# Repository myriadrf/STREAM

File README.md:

# STREAM

[STREAM](https://myriadrf.org/projects/stream/) is a flexible platform for developing high-performance digital and RF designs using an Altera Cyclone IV FPGA and Lime Microsystems FPRF transceiver.

The original STREAM board incorporates SDRAM, Micro SD storage and a selection of other useful peripherals, with expansion via RFDIO and FMC mezzanine cards enabling use with both LMS6002-based Myriad-RF 1 and UNITE LMS7002M EVB RF modules.

uSTREAM is a low cost variant that incorporates a uRFDIO connector, enabling use with the uMyriadRF-6002 and uMyriadRF-7002 RF modules.

For more details about compatible Myriad-RF transceiver modules, see the [Reference Development Kit](https://myriadrf.org/projects/rdk/).

## Contents

The directory structure is as follows:

      apps/
          lms6_usb_distro_03v/        - uSTREAM + uMyriadRF-6002 examples
          lms7_usb_distro_01v/        - uSTREAM + uMyriadRF-7002 examples
          STREAM_LMS7EVB_distro_07v/  - STREAM + UNITE LMS7002EVB examples

      docs/                      - platform documentation

      hardware/<variant>/<version>/
          BOM/                   - bill of materials spreadsheet
          Case/                  - Aluminium case design
          Gerbers/               - Gerber CAM files
          KiCAD/                 - KiCAD schematic and layout files
          Manufacturing/         - Additional manufacturing information
          PDF/                   - Schematic and layout PDFs
          Reports/               - DRC, ERC and drill reports
              
      stream_openrisc_soc/
          bin/                   - pre-built FPGA and Linux images
          doc/                   - HTML documentation for the Stream OpenRISC SoC
          quartus/               - Quartus project archive for rebuilding the FPGA image
          src/                   - Source code for Stream-specific cores
          sw/                    - Example applications for communicating with LMS6002D

## Licensing

### Hardware

The hardware designs are licensed under a Creative Commons Attribution 3.0 Unported licence.

### FPGA design

For details of the FPGA design licensing please see the associated COPYING file(s). However, please note that this does not extend to any files provided with the Altera design tools and see the relevant files for the associated terms and conditions.

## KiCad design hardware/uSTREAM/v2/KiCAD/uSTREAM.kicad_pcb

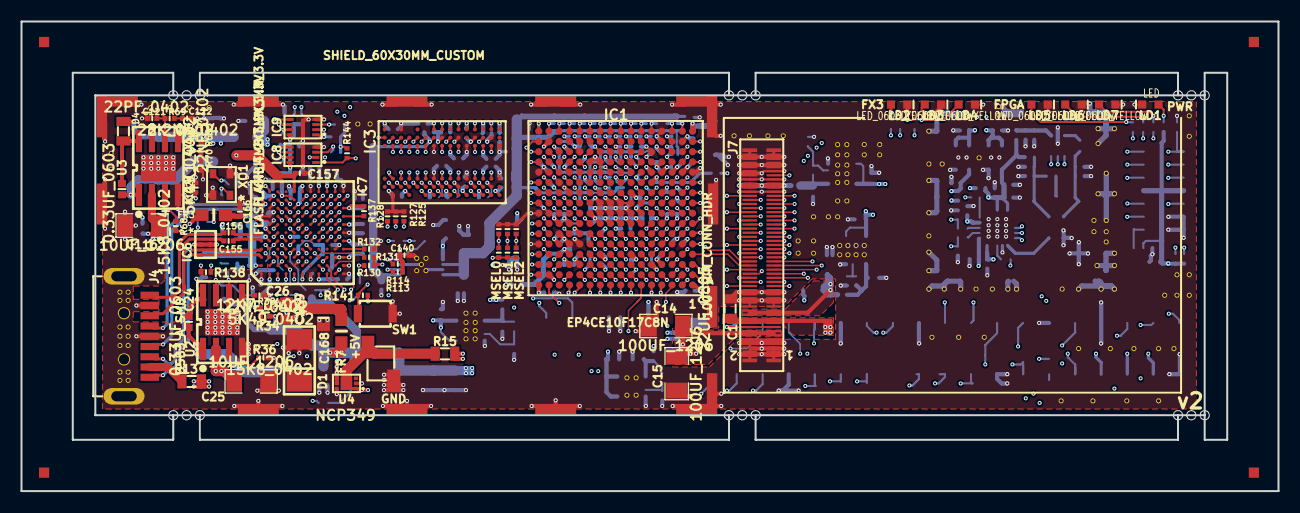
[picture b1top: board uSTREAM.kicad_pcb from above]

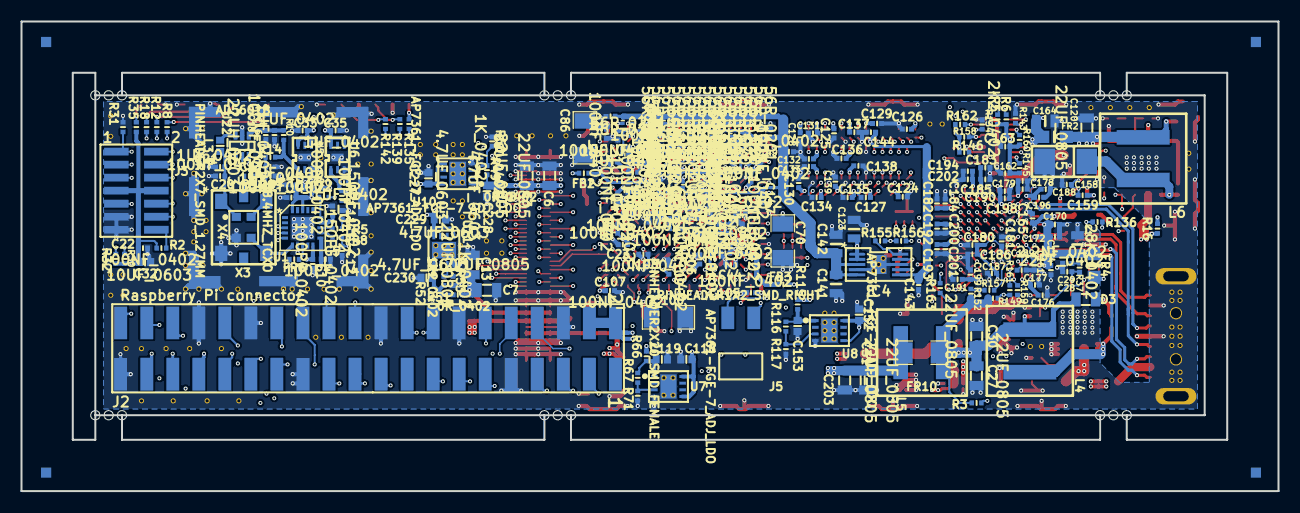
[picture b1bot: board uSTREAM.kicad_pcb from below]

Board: 12 copper layers, 122.6 x 45.8 mm, 491 parts (270 on the bottom side), 284 nets.

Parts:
BreakHole: VAL**; BreakHole
BreakHole#2, BreakHole#3, BreakHole#4, BreakHole#5, BreakHole#6, BreakHole#7, BreakHole#8, BreakHole#9, BreakHole#10, BreakHole#11, BreakHole#12, BreakHole#13, BreakHole#14, BreakHole#15, BreakHole#16, BreakHole#17, BreakHole#18: VAL**; BreakHole
C1, C3, C6, C7, C13, C27, C30, C31, C120, C203: 22UF_0805; SMD0805
C4, C5, C8, C9, C10: 100PF_0402; SMD0402
C11, C12: 150PF_0402; SMD0402
C14, C15: 100UF_1206; SMD1206
C16, C17, C20, C33, C34, C35, C36, C73, C76, C79, C82, C85, C96, C99: 1UF_0402; SMD0402
C18, C19, C21, C22, C23, C44, C64, C72, C75, C78, C81, C84, C87, C88, C89, C90, C91, C92, C95, C98, C101, C102, C103, C104, C105, C106, C107, C108, C109, C110, C112: 100NF_0402; SMD0402
C24, C115: 0.33UF_0603; SMD0603
C25, C116: 10UF_1206; SMD1206
C26, C117: 22NF_0402; SMD0402
C28, C121: 22PF_0402; SMD0402
C29, C122: 2.2NF_0402; SMD0402
C32: 10UF_0603; SMD0603
C70, C86, C100: 100UF_1206; SM1206
C71, C74, C77, C80, C83, C94, C97: 10NF_0402; SM0402
C113, C114, C124, C125, C126, C127, C128, C129, C130, C131, C132, C133, C134, C135, C136, C137, C138, C139, C143, C144, C146, C147, C148, C149, C150, C151, C155, C156, C161, C162, C163, C166, C170, C172, C174, C176, C178, C180, C182, C183, C186, C188, C189, C190, C191, C192, C193, C194: 100NF_0402; C_SM0402
C118, C119, C152, C153: 4.7UF_0603; C_SM0603
C123, C141, C142: 10UF_0805; C_SM0805
C140, C157: 1UF_0402; C_SM0402
C158, C159: 13PF_0402; C_SM0402
C164, C168, C169, C171: 22UF_0805; C_SM0805
C165, C177, C179, C181, C184, C185, C187, C196, C198, C199, C200, C201, C202: 10NF_0402; C_SM0402
C227, C228, C229, C230: 4.7UF_0603; SMD0603
D1, D2: 20BQ030; SMB
D3, D4: TS4148; SM0805
EK1: SHIELD_60X30MM_CUSTOM; shield_60x30mm_custom
EK2: SHIELD_16.5X16.5MM; shield_16.5x16.5mm
FB1, FB2, FB3, FB4: FB_600R_0402; R_SM0402
FD1, FD2, FD3, FD4: FIDUCIAL; Pad
FR2, FR3, FR4, FR7: FR_600R_0805_2A; R_SM0805
FR5, FR6, FR8, FR9: FR_220R_0402; R_SM0402
FR10: FR_220R_1206_4A; SM1206
GND_VIA: VAL**; GND_VIA
GND_VIA#2, GND_VIA#3, GND_VIA#4, GND_VIA#5, GND_VIA#6, GND_VIA#7, GND_VIA#8, GND_VIA#9, GND_VIA#10, GND_VIA#11, GND_VIA#12, GND_VIA#13, GND_VIA#14, GND_VIA#15, GND_VIA#16, GND_VIA#17, GND_VIA#18, GND_VIA#19, GND_VIA#20, GND_VIA#21, GND_VIA#22, GND_VIA#23, GND_VIA#24, GND_VIA#25, GND_VIA#26, GND_VIA#27, GND_VIA#28, GND_VIA#29, GND_VIA#30, GND_VIA#31, GND_VIA#32, GND_VIA#33, GND_VIA#34, GND_VIA#35, GND_VIA#36, GND_VIA#37, GND_VIA#38, GND_VIA#39, GND_VIA#40, GND_VIA#41, GND_VIA#42, GND_VIA#43, GND_VIA#44, GND_VIA#45, GND_VIA#46, GND_VIA#47, GND_VIA#48, GND_VIA#49, GND_VIA#50, GND_VIA#51, GND_VIA#52, GND_VIA#53, GND_VIA#54, GND_VIA#55, GND_VIA#56, GND_VIA#57, GND_VIA#58, GND_VIA#59, GND_VIA#60, GND_VIA#61, GND_VIA#62, GND_VIA#63, GND_VIA#64, GND_VIA#65, GND_VIA#66, GND_VIA#67, GND_VIA#68, GND_VIA#69, GND_VIA#70, GND_VIA#71, GND_VIA#72, GND_VIA#73, GND_VIA#74, GND_VIA#75, GND_VIA#76, GND_VIA#77, GND_VIA#78, GND_VIA#79, GND_VIA#80, GND_VIA#81, GND_VIA#82, GND_VIA#83, GND_VIA#84, GND_VIA#85, GND_VIA#86, GND_VIA#87, GND_VIA#88, GND_VIA#89, GND_VIA#90, GND_VIA#91, GND_VIA#92, GND_VIA#93, GND_VIA#94, GND_VIA#95, GND_VIA#96, GND_VIA#97, GND_VIA#98, GND_VIA#99, GND_VIA#100, GND_VIA#101, GND_VIA#102, GND_VIA#103, GND_VIA#104, GND_VIA#105, GND_VIA#106, GND_VIA#107, GND_VIA#108, GND_VIA#109, GND_VIA#110, GND_VIA#111, GND_VIA#112, GND_VIA#113, GND_VIA#114, GND_VIA#115, GND_VIA#116, GND_VIA#117, GND_VIA#118, GND_VIA#119, GND_VIA#120, GND_VIA#121, GND_VIA#122, GND_VIA#123, GND_VIA#124, GND_VIA#125, GND_VIA#126, GND_VIA#127: VAL**; GND_VIA
IC1: EP4CE10F17C8N; 256FBGA
IC3: W9751G6KB-25; 84WBGA
IC4: RT9026GFP; MSOP10
IC6: SP3010-04UTG; uDFN-10
IC7: CYUSB3013; FBGA_121_Ball_10x10
IC8, IC9: FLASH_4MBIT_2X3MM_3.3V; 8-USON
J1: JUMPER2_V; PINHEADER_1x2_SMD
J2: PINHEADER2X20_SMD_FEMALE; PinHeader2x20SMDfemale
J3: PINHEADER2X7_SMD_1.27MM; PinHeader2x7_SMD_1.27mm
J4: USB3_A_SMD
J5: PINHEADER1X2_SMD_RIGHT; PINHEADER_1x2_SMD_right
J7: 100-PIN_CONN_HDR
L3: 22UH_0603; SMD0603
L4: 2.2UH_XAL60XX_SERIES; XAL60xx series
L5: 22UH_XAL60XX_SERIES_NF; XAL60xx series
L6: 22UH_XAL60XX_SERIES; XAL60xx series
LD1: LED; LD0603
LD2, LD3, LD4, LD5, LD6, LD7: LED_0603_YELLOW; LD0603
R2, R141, R143: 100K_0402; R_SM0402
R3, R5, R6, R67: 2K2_0402; R_SM0402
R8, R12, R31, R71, R117, R135, R139, R142: 1K_0402; R_SM0402
R9, R18, R21, R66, R115, R132, R147, R150, R153, R156, R157, R159, R161, R163: 0R_0402; R_SM0402
R10, R14, R16: 100MHz/600/0.2A; R_SM0402
R13, R15: 0R_0805; SM0805
R20, R122, R148, R151, R154: 0R_0402_NF; R_SM0402
R22: 10K_0402; SMD0402
R30, R32, R113, R114, R125, R127, R128, R130, R149, R152, R155: 10K_0402; R_SM0402
R34: 12K7_0402; SMD0402
R35: 806R_0402; R_SM0402
R36, R68: 15K8_0402; SMD0402
R37, R69: 28K_0402; SMD0402
R38, R70: 5K49_0402; SMD0402
R48, R51: 0R_0402; SM0402
R49: 560_0402; SM0402
R50, R53: 1K_0402; SMD0402
R52: 1K2_0402; SM0402
R65: 1K1_0402; SMD0402
R72, R73, R74, R75, R76, R77, R78, R79, R80, R81, R82, R83, R84, R85, R86, R87, R88, R89, R90, R91, R92, R93, R94, R95, R96, R97, R98, R99, R100, R101, R102, R103, R104, R105, R106, R107, R108, R109, R110, R111, R112: 56R_0201; SMD0201
R116: 1K2_0402; R_SM0402
R131, R137: 10K_0402_NF; R_SM0402
R134: 2K2_0402; SMD0402
R136: 6.04K/1%_0402; R_SM0402
R138: 200R/1%_0402; R_SM0402
R144, R145, R146, R158, R160, R162: 4K7_0402; R_SM0402
SW1: SW_TACTILE; SW_B3U-1000P
U1: SI5351C; QFN20
U2, U3: SC4524; SOIC-8
U4: NCP349; 6-DFN
U5: LP5900SD-3.3; SC70
U6: LP5900SD-1.8; SC70
U7, U8, U10, U11: AP7361-FGE-7_ADJ_LDO; 8-UDFN3030
U22: AD5601B; SC-70-6
X3: RACON_TXCO_PLUTO+; SMD_TXCO_Pluto+
X4: 38.4MHZ_TCXO; TCXO_2x2.5mm
XO1: CRYSTAL_19.2MHZ; 4-SMD_TCXO

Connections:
+1.8V: C7.1, C13.1, J7.21, J7.22, J7.23, J7.24, R51.2
+1.8VD: C86.1, C87.1, C88.1, C89.1, C90.1, C91.1, C92.1, C101.1, C102.1, C103.1, C104.1, C123.1, C124.1, C125.1, C126.1, C127.1, C128.1, C129.1, C130.1, C131.1, C132.1, C133.1, C134.1, C135.1, C136.1, C137.1, C138.1, C139.1, C182.1, C183.1, C184.1, C185.1, IC1.E14, IC1.G14, IC1.K14, IC1.M14, IC1.P4, IC1.P7, IC1.P10, IC1.P13, IC1.T1, IC1.T16, IC3.A1, IC3.A9, IC3.C1, IC3.C3, IC3.C7, IC3.C9, IC3.E1, IC3.E9, IC3.G1, IC3.G3, IC3.G7, IC3.G9, IC3.J1, IC3.J9, IC3.M9, IC3.R1, IC4.1, IC4.2, IC7.H11, IC7.L9, R115.2, R130.2, R131.2, R137.2
+1.8V_CLK: C10.1, C36.1, R21.2, U1.10, U6.1
+1.25V: C3.1, C6.1, J7.83, J7.84, J7.85, J7.86, R48.2
+3.3VD: C23.1, C27.1, C30.1, C44.1, C64.1, C100.1, C105.1, C106.1, C107.1, C108.1, C109.1, C110.1, C112.1, C140.1, C152.1, C162.1, C163.1, D3.1, FR3.2, FR7.1, FR10.1, IC1.A1, IC1.A16, IC1.C4, IC1.C7, IC1.C10, IC1.C13, IC1.E3, IC1.G3, IC1.K3, IC1.M3, IC4.10, IC8.8, IC9.8, L4.1, L5.2, R3.1, R5.1, R6.1, R22.1, R34.1, R113.1, R114.1, R141.2, R144.1, R145.1, R146.1, R149.1, R152.1, R155.1, R158.1, R160.1, R162.1, U8.5, U8.8
+3.3V_CLK: C4.1, C8.1, C9.1, C34.1, R10.2, R14.2, R20.2, U1.14, U1.18, U1.20, U5.1
+3.3Va: C1.1, C22.1, C31.1, C32.1, C118.1, C203.1, C227.1, C229.1, FR10.2, J3.7, J3.8, J7.17, J7.18, J7.19, J7.20, L5.1, R2.2, R30.2, R32.2, R35.2, U7.5, U7.8, U10.5, U10.8, U11.5, U11.8
+5V: C14.1, C15.1, C25.1, C33.1, C35.1, C116.1, J7.11, J7.12, J7.13, J7.14, R16.1, U2.2, U3.2, U4.4, U4.5, U5.4, U5.6, U6.4, U6.6
+5V_RPi: J2.2, J2.4, R15.2
+5V_USB: J4.1, R13.1
/FX3/D+: IC7.A9, J4.3
/FX3/D-: IC7.A10, J4.2
/FX3/FX3_FLASH1_SNN: IC7.C1, J5.2
/FX3/FX3_FLASH2_SNN: IC7.F2, IC9.1, R158.2
/FX3/FX3_LED0: IC7.H2, R135.1
/FX3/FX3_LED1: IC7.H3, R139.1
/FX3/FX3_LED2: IC7.K1, R142.1
/FX3/MSEL0: IC1.H13, R147.1, R148.2
/FX3/MSEL1: IC1.H12, R150.1, R151.2
/FX3/MSEL2: IC1.G12, R153.1, R154.2
/FX3/OTG_ID: IC7.C9, R122.1
/FX3/SSRX+: IC6.5, IC6.6, IC7.A3, J4.9
/FX3/SSRX-: IC6.4, IC6.7, IC7.A4, J4.8
/FX3/SSTX+: C155.1, IC6.2, IC6.9, J4.6
/FX3/SSTX-: C156.1, IC6.1, IC6.10, J4.5
/LMS Digital Circuits/CLK_IO: C5.1, R20.1, R21.1, U1.11
/RaspberryPi_Connector/LD5: IC1.E11, R8.1
/RaspberryPi_Connector/LD6: IC1.E10, R12.1
/RaspberryPi_Connector/RPI_CE0n: IC1.A7, J2.24
/RaspberryPi_Connector/RPI_CE1n: IC1.C9, J2.26
/RaspberryPi_Connector/RPI_GCLK: IC1.B13, J2.7
/RaspberryPi_Connector/RPI_GEN0: IC1.D12, J2.11
/RaspberryPi_Connector/RPI_GEN1: IC1.A12, J2.12
/RaspberryPi_Connector/RPI_GEN2: IC1.B12, J2.13
/RaspberryPi_Connector/RPI_GEN3: IC1.A11, J2.15
/RaspberryPi_Connector/RPI_GEN4: IC1.B11, J2.16
/RaspberryPi_Connector/RPI_GEN5: IC1.A10, J2.18
/RaspberryPi_Connector/RPI_GEN6: IC1.B9, J2.22
/RaspberryPi_Connector/RPI_GPIO5: IC1.B8, J2.29
/RaspberryPi_Connector/RPI_GPIO6: IC1.D9, J2.31
/RaspberryPi_Connector/RPI_GPIO12: IC1.D8, J2.32
/RaspberryPi_Connector/RPI_GPIO13: IC1.F11, J2.33
/RaspberryPi_Connector/RPI_GPIO16: IC1.E8, J2.36
/RaspberryPi_Connector/RPI_GPIO19: IC1.E9, J2.35
/RaspberryPi_Connector/RPI_GPIO20: IC1.F8, J2.38
/RaspberryPi_Connector/RPI_GPIO21: IC1.F9, J2.40
/RaspberryPi_Connector/RPI_GPIO26: IC1.F10, J2.37
/RaspberryPi_Connector/RPI_ID_SC: IC1.C8, J2.28
/RaspberryPi_Connector/RPI_ID_SD: IC1.D11, J2.27
/RaspberryPi_Connector/RPI_MISO: IC1.A9, J2.21
/RaspberryPi_Connector/RPI_MOSI: IC1.B10, J2.19
/RaspberryPi_Connector/RPI_RXD0: IC1.C11, J2.10
/RaspberryPi_Connector/RPI_SCLK: IC1.A8, J2.23
/RaspberryPi_Connector/RPI_TXD0: IC1.C6, J2.8
/RaspberryPi_Connector/VCCA1: C97.1, C98.1, C99.1, FB2.2, IC1.L5
/RaspberryPi_Connector/VCCA2: C94.1, C95.1, C96.1, FB1.2, IC1.F12
/RaspberryPi_Connector/VCCD_PLL1: C83.1, C84.1, C85.1, FB4.2, IC1.N4
/RaspberryPi_Connector/VCCD_PLL2: C80.1, C81.1, C82.1, FB3.2, IC1.D13
DDR_A0: IC1.K10, IC3.M8, R92.2
DDR_A1: IC1.T8, IC3.M3, R93.2
DDR_A2: IC1.L9, IC3.M7, R94.2
DDR_A3: IC1.T10, IC3.N2, R95.2
DDR_A4: IC1.N3, IC3.N8, R96.2
DDR_A5: IC1.T9, IC3.N3, R97.2
DDR_A6: IC1.K9, IC3.N7, R98.2
DDR_A7: IC1.T15, IC3.P2, R99.2
DDR_A8: IC1.P14, IC3.P8, R100.2
DDR_A9: IC1.T11, IC3.P3, R101.2
DDR_A10: IC1.T6, IC3.M2, R102.2
DDR_A11: IC1.R13, IC3.P7, R103.2
DDR_A12: IC1.T14, IC3.R2, R104.2
DDR_B0: IC1.T5, IC3.L2, R105.2
DDR_B1: IC1.T3, IC3.L3, R106.2
DDR_CKE: IC1.T2, IC3.K2, R112.2
DDR_CLKn: IC1.N12, IC3.K8
DDR_CLKp: IC1.M11, IC3.J8
DDR_DQ0: IC1.N6, IC3.G8, R72.2
DDR_DQ1: IC1.R6, IC3.G2, R73.2
DDR_DQ2: IC1.N5, IC3.H7, R74.2
DDR_DQ3: IC1.R7, IC3.H3, R75.2
DDR_DQ4: IC1.R5, IC3.H1, R76.2
DDR_DQ5: IC1.L7, IC3.H9, R77.2
DDR_DQ6: IC1.R3, IC3.F1, R78.2
DDR_DQ7: IC1.L8, IC3.F9, R79.2
DDR_DQ8: IC1.R11, IC3.C8, R80.2
DDR_DQ9: IC1.R10, IC3.C2, R81.2
DDR_DQ10: IC1.N8, IC3.D7, R82.2
DDR_DQ11: IC1.R12, IC3.D3, R83.2
DDR_DQ12: IC1.T12, IC3.D1, R84.2
DDR_DQ13: IC1.N9, IC3.D9, R85.2
DDR_DQ14: IC1.T13, IC3.B1, R86.2
DDR_DQ15: IC1.P8, IC3.B9, R87.2
DDR_LDM: IC1.P3, IC3.F3, R90.2
DDR_LDQS: IC1.M7, IC3.F7, R88.2
DDR_ODT: IC1.R8, IC3.K9, R111.2
DDR_UDM: IC1.M8, IC3.B3, R91.2
DDR_UDQS: IC1.T7, IC3.B7, R89.2
DDR_nCAS: IC1.L11, IC3.L7, R108.2
DDR_nCS: IC1.L10, IC3.L8, R110.2
DDR_nRAS: IC1.M9, IC3.K7, R107.2
DDR_nWE: IC1.R9, IC3.K3, R109.2
DIG_RST: IC1.D6, J7.44
DIQ1_D0: IC1.L1, J7.74
DIQ1_D1: IC1.L2, J7.76
DIQ1_D2: IC1.P1, J7.79
DIQ1_D3: IC1.K1, J7.72
DIQ1_D4: IC1.K5, J7.70
DIQ1_D5: IC1.L6, J7.78
DIQ1_D6: IC1.P2, J7.77
DIQ1_D7: IC1.R1, J7.75
DIQ1_D8: IC1.K6, J7.68
DIQ1_D9: IC1.N2, J7.73
DIQ1_D10: IC1.L4, J7.80
DIQ1_D11: IC1.J1, J7.66
DIQ2_D0: IC1.D4, J7.52
DIQ2_D1: IC1.B6, J7.49
DIQ2_D2: IC1.D3, J7.50
DIQ2_D3: IC1.B1, J7.51
DIQ2_D4: IC1.F2, J7.56
DIQ2_D5: IC1.E5, J7.54
DIQ2_D6: IC1.F1, J7.58
DIQ2_D7: IC1.B3, J7.53
DIQ2_D8: IC1.G1, J7.60
DIQ2_D9: IC1.C1, J7.55
DIQ2_D10: IC1.J2, J7.64
DIQ2_D11: IC1.G2, J7.62
ENABLE_IQSEL1: IC1.J6, J7.67
ENABLE_IQSEL2: IC1.C3, J7.59
FCLK1: IC1.K2, J7.69
FCLK2: IC1.D2, J7.61
FPGA_CLK4: FR6.2, IC1.E15
FPGA_CONF_DONE: IC1.H14, R155.2, R156.1
FPGA_DAC_CS: IC1.B5, U22.1
FPGA_DATA0: IC1.H2, R159.1
FPGA_DCLK: IC1.H1, R163.1
FPGA_LMS_CS: IC1.A2, J7.38
FPGA_NCONFIG: IC1.H5, R149.2, R161.1
FPGA_NSTATUS: IC1.F4, R152.2, R157.1
FPGA_SPI_MISO: IC1.E6, J7.37
FPGA_SPI_MOSI: IC1.A5, J7.36, U22.3
FPGA_SPI_SCK: IC1.E7, J7.40, U22.2
FX3_CONF_DONE: IC7.E5, R156.2
FX3_CTL0: IC1.K15, IC7.K8
FX3_CTL1: IC1.J15, IC7.K7
FX3_CTL2: IC1.F13, IC7.J7
FX3_CTL3: IC1.D15, IC7.H7
FX3_CTL4: IC1.B16, IC7.G7
FX3_CTL5: IC1.F15, IC7.G6
FX3_CTL6: IC1.J14, IC7.K6
FX3_CTL7: IC1.J12, IC7.H8
FX3_CTL8: IC1.G16, IC7.G5
FX3_CTL9: IC1.C16, IC7.H6
FX3_CTL10: IC1.J16, IC7.K5
FX3_CTL11: IC1.J13, IC7.J5
FX3_CTL12: IC1.G15, IC7.H5
FX3_DATA0: IC7.D1, R159.2
FX3_DCLK: IC7.D3, R163.2
FX3_DQ0: IC1.P16, IC7.F10
FX3_DQ1: IC1.R16, IC7.F9
FX3_DQ2: IC1.F16, IC7.F7
FX3_DQ3: IC1.N13, IC7.G10
FX3_DQ4: IC1.K11, IC7.G9
FX3_DQ5: IC1.J11, IC7.F8
FX3_DQ6: IC1.N15, IC7.H10
FX3_DQ7: IC1.K12, IC7.H9
FX3_DQ8: IC1.N16, IC7.J10
FX3_DQ9: IC1.L16, IC7.J9
FX3_DQ10: IC1.M12, IC7.K11
FX3_DQ11: IC1.L15, IC7.L10
FX3_DQ12: IC1.L13, IC7.K10
FX3_DQ13: IC1.L12, IC7.K9
FX3_DQ14: IC1.K16, IC7.J8
FX3_DQ15: IC1.G11, IC7.G8
FX3_FPGA_GPIO0: IC1.B4, IC7.K2
FX3_FPGA_GPIO1: IC1.A4, IC7.J2
FX3_FPGA_GPIO2: IC1.D5, IC7.J3
FX3_FPGA_GPIO3: IC1.A3, IC7.J1
FX3_FPGA_SNN: IC1.A6, IC7.E1
FX3_NCONFIG: IC7.D2, R161.2
FX3_NSTATUS: IC7.E4, R157.2
FX3_PCLK: IC1.D16, IC7.J6
FX3_SPI_MISO: IC1.F6, IC7.C2, IC8.2, IC9.2, R134.1
FX3_SPI_MOSI: IC1.F7, IC7.D5, IC8.5, IC9.5
FX3_SPI_SCK: IC1.B7, IC7.D4, IC8.6, IC9.6, R143.1
FX3_VCC3P3: C168.1, C169.1, C176.1, C177.1, C178.1, C179.1, C180.1, C181.1, C186.1, C187.1, FR7.2, IC7.B1, IC7.C11, IC7.E3, IC7.E10, IC7.F1
FX3_VDD: C164.1, C188.1, C189.1, C190.1, C191.1, C192.1, C193.1, C194.1, C196.1, C198.1, C199.1, C200.1, C201.1, C202.1, FR2.2, FR4.2, IC7.B10, IC7.C3, IC7.E9, IC7.F11, IC7.H1, IC7.J11, IC7.L5, IC7.L7
GND: C1.2, C3.2, C4.2, C5.2, C6.2, C7.2, C8.2, C9.2, C10.2, C11.2, C12.2, C13.2, C14.2, C15.2, C16.2, C17.2, C18.2, C19.2, C20.2, C21.2, C22.2, C23.2, C25.2, C26.2, C27.2, C28.2, C29.2, C30.2, C31.2, C32.2, C33.2, C34.2, C35.2, C36.2, C44.2, C64.2, C70.2, C71.2, C72.2, C73.2, C74.2, C75.2, C76.2, C77.2, C78.2, C79.2, C80.2, C81.2, C82.2, C83.2, C84.2, C85.2, C86.2, C87.2, C88.2, C89.2, C90.2, C91.2, C92.2, C94.2, C95.2, C96.2, C97.2, C98.2, C99.2, C100.2, C101.2, C102.2, C103.2, C104.2, C105.2, C106.2, C107.2, C108.2, C109.2, C110.2, C112.2, C113.2, C114.2, C116.2, C117.2, C118.2, C119.2, C120.2, C121.2, C122.2, C123.2, C124.2, C125.2, C126.2, C127.2, C128.2, C129.2, C130.2, C131.2, C132.2, C133.2, C134.2, C135.2, C136.2, C137.2, C138.2, C139.2, C140.2, C141.2, C142.2, C143.2, C144.2, C146.2, C147.2, C148.2, C149.2, C150.2, C151.2, C152.2, C153.2, C157.2, C158.1, C159.1, C161.2, C162.2, C163.2, C164.2, C165.2, C166.2, C168.2, C169.2, C170.2, C171.2, C172.2, C174.2, C176.2, C177.2, C178.2, C179.2, C180.2, C181.2, C182.2, C183.2, C184.2, C185.2, C186.2, C187.2, C188.2, C189.2, C190.2, C191.2, C192.2, C193.2, C194.2, C196.2, C198.2, C199.2, C200.2, C201.2, C202.2, C203.2, C227.2, C228.2, C229.2, C230.2, D1.1, D2.1, EK1.1, EK2.1, GND_VIA.1, GND_VIA#2.1, GND_VIA#3.1, GND_VIA#4.1, GND_VIA#5.1, GND_VIA#6.1, GND_VIA#7.1, GND_VIA#8.1, GND_VIA#9.1, GND_VIA#10.1, GND_VIA#11.1, GND_VIA#12.1, GND_VIA#13.1, GND_VIA#14.1, GND_VIA#15.1, GND_VIA#16.1, GND_VIA#17.1, GND_VIA#18.1, GND_VIA#19.1, GND_VIA#20.1, GND_VIA#21.1, GND_VIA#22.1, GND_VIA#23.1, GND_VIA#24.1, GND_VIA#25.1, GND_VIA#26.1, GND_VIA#27.1, GND_VIA#28.1, GND_VIA#29.1, GND_VIA#30.1, GND_VIA#31.1, GND_VIA#32.1, GND_VIA#33.1, GND_VIA#34.1, GND_VIA#35.1, GND_VIA#36.1, GND_VIA#37.1, GND_VIA#38.1, GND_VIA#39.1, GND_VIA#40.1, GND_VIA#41.1, GND_VIA#42.1, GND_VIA#43.1, GND_VIA#44.1, GND_VIA#45.1, GND_VIA#46.1, GND_VIA#47.1, GND_VIA#48.1, GND_VIA#49.1, GND_VIA#50.1, GND_VIA#51.1, GND_VIA#52.1, GND_VIA#53.1, GND_VIA#54.1, GND_VIA#55.1, GND_VIA#56.1, GND_VIA#57.1, GND_VIA#58.1, GND_VIA#59.1, GND_VIA#60.1, GND_VIA#61.1, GND_VIA#62.1, GND_VIA#63.1, GND_VIA#64.1, GND_VIA#65.1, GND_VIA#66.1, GND_VIA#67.1, GND_VIA#68.1, GND_VIA#69.1, GND_VIA#70.1, GND_VIA#71.1, GND_VIA#72.1, GND_VIA#73.1, GND_VIA#74.1, GND_VIA#75.1, GND_VIA#76.1, GND_VIA#77.1, GND_VIA#78.1, GND_VIA#79.1, GND_VIA#80.1, GND_VIA#81.1, GND_VIA#82.1, GND_VIA#83.1, GND_VIA#84.1, GND_VIA#85.1, GND_VIA#86.1, GND_VIA#87.1, GND_VIA#88.1, GND_VIA#89.1, GND_VIA#90.1, GND_VIA#91.1, GND_VIA#92.1, GND_VIA#93.1, GND_VIA#94.1, GND_VIA#95.1, GND_VIA#96.1, GND_VIA#97.1, GND_VIA#98.1, GND_VIA#99.1, GND_VIA#100.1, GND_VIA#101.1, GND_VIA#102.1, GND_VIA#103.1, GND_VIA#104.1, GND_VIA#105.1, GND_VIA#106.1, GND_VIA#107.1, GND_VIA#108.1, GND_VIA#109.1, GND_VIA#110.1, GND_VIA#111.1, GND_VIA#112.1, GND_VIA#113.1, GND_VIA#114.1, GND_VIA#115.1, GND_VIA#116.1, GND_VIA#117.1, GND_VIA#118.1, GND_VIA#119.1, GND_VIA#120.1, GND_VIA#121.1, GND_VIA#122.1, GND_VIA#123.1, GND_VIA#124.1, GND_VIA#125.1, GND_VIA#126.1, GND_VIA#127.1, IC1.B2, IC1.B15, IC1.C5, IC1.C12, IC1.D7, IC1.D10, IC1.E2, IC1.E4, IC1.E12, IC1.E13, IC1.E16, IC1.F14, IC1.G4, IC1.G13, IC1.H7, IC1.H8, IC1.H9, IC1.H10, IC1.H15, IC1.H16, IC1.J3, IC1.J7, IC1.J8, IC1.J9, IC1.J10, IC1.K4, IC1.K13, IC1.L14, IC1.M1, IC1.M2, IC1.M4, IC1.M5, IC1.M10, IC1.M13, IC1.M15, IC1.M16, IC1.N7, IC1.N10, IC1.N11, IC1.P5, IC1.P12, IC1.R2, IC1.R4, IC1.R15, IC1.T4, IC3.A3, IC3.A7, IC3.B2, IC3.B8, IC3.D2, IC3.D8, IC3.E3, IC3.E7, IC3.F2, IC3.F8, IC3.H2, IC3.H8, IC3.J3, IC3.J7, IC3.N1, IC3.P9, IC4.4, IC4.8, IC4.11, IC6.3, IC6.8, IC7.A1, IC7.A8, IC7.B7, IC7.B8, IC7.B9, IC7.D8, IC7.E2, IC7.G1, IC7.G11, IC7.K3, IC7.K4, IC7.L1, IC7.L2, IC7.L3, IC7.L6, IC7.L11, IC8.4, IC8.9, IC9.4, IC9.9, J1.1, J2.6, J2.9, J2.14, J2.20, J2.25, J2.30, J2.34, J2.39, J3.11, J3.13, J4.4, J4.7, J4.10, J7.0, J7.1, J7.2, J7.3, J7.4, J7.5, J7.6, J7.7, J7.8, J7.9, J7.10, J7.15, J7.16, J7.25, J7.26, J7.27, J7.28, J7.29, J7.30, J7.31, J7.32, J7.33, J7.34, J7.81, J7.82, J7.87, J7.88, J7.90, J7.91, J7.92, J7.93, J7.94, J7.95, J7.96, J7.97, J7.98, J7.99, J7.100, LD1.2, LD2.2, LD3.2, LD4.2, LD5.2, LD6.2, LD7.2, R31.1, R36.2, R38.2, R50.1, R53.1, R68.2, R70.2, R71.2, R117.2, R122.2, R125.1, R127.1, R128.1, R132.2, R134.2, R136.2, R138.2, R143.2, R147.2, R150.2, R153.2, SW1.1, U1.7, U1.21, U2.4, U2.9, U3.4, U3.9, U4.2, U4.6, U5.3, U5.7, U6.3, U6.7, U7.4, U7.9, U8.4, U8.9, U10.4, U10.9, U11.4, U11.9, U22.5, X3.2, X4.2, XO1.2, XO1.4
GPIO0: IC1.P9, J7.39
GPIO1: IC1.L3, J7.41
GPIO2: IC1.N14, J7.43
GPIO3: IC1.P15, J7.45
G_PWR_DWN: IC1.D1, J7.46
I2C_SCL: IC1.C14, IC7.D9, J2.5, R6.2, U1.4
I2C_SDA: IC1.D14, IC7.D10, J2.3, R5.2, U1.5
LD7: IC1.K8, R18.1
MCLK1: IC1.N1, J7.71
MCLK2: IC1.C2, J7.57
unnamed: J3.14, R2.1
unnamed: U1.6, X3.4, X4.3
unnamed: FR6.1, U1.8
unnamed: FR9.1, U1.15
unnamed: FR8.1, U1.12
unnamed: FR9.2, IC1.E1
unnamed: FR5.1, U1.13
unnamed: C16.1, C18.1, R10.1, U22.4
unnamed: R9.1, X3.6
unnamed: L3.2, U22.6
unnamed: C17.1, C19.1, R9.2, R14.1, X3.5, X4.4
unnamed: C20.1, C21.1, L3.1, X3.1, X4.1
unnamed: C158.2, IC7.C7, XO1.3
unnamed: C159.2, IC7.C6, XO1.1
unnamed: IC7.B3, R138.1
unnamed: IC7.E6, R128.2
unnamed: IC7.B4, R127.2
unnamed: C161.1, IC7.C5, R141.1, SW1.2
unnamed: C156.2, IC7.A6
unnamed: IC7.L4, R132.1
unnamed: IC7.G4, R130.1
unnamed: IC7.H4, R131.1
unnamed: LD3.1, R139.2
unnamed: IC7.L8, R137.1
unnamed: IC9.7, R160.2
unnamed: IC9.3, R162.2
unnamed: IC7.C8, R136.1
unnamed: LD2.1, R135.2
unnamed: LD4.1, R142.2
unnamed: IC8.3, R146.2
unnamed: IC8.7, R145.2
unnamed: IC8.1, J5.1, R144.2
unnamed: C155.2, IC7.A5
unnamed: C157.1, IC7.E11, R16.2
unnamed: IC7.B2, R125.2
unnamed: C170.1, C171.1, C172.1, C174.1, FR4.1, IC7.A2, IC7.A7, IC7.B5
unnamed: C165.1, C166.1, FR3.1, IC7.B6
unnamed: LD7.1, R18.2
unnamed: LD6.1, R12.2
unnamed: LD5.1, R8.2
unnamed: IC4.9, R114.2
unnamed: IC4.7, R113.2
unnamed: C117.1, U3.5
unnamed: R68.1, U3.3
unnamed: C122.1, R69.2
unnamed: C115.2, D2.2, L6.2, U3.1
unnamed: C115.1, D4.2, U3.8
unnamed: C121.1, R69.1, U3.6
unnamed: R65.2, R70.1, U3.7
unnamed: C119.1, R66.1, R67.1, U7.1
unnamed: R67.2, R71.1, U7.3
unnamed: C153.1, R115.1, R116.2, U8.1
unnamed: C228.1, R48.1, R49.1, U10.1
unnamed: C230.1, R51.1, R52.2, U11.1
unnamed: R116.1, R117.1, U8.3
unnamed: C24.1, D3.2, U2.8
unnamed: C28.1, R37.1, U2.6
unnamed: R36.1, U2.3
unnamed: C26.1, U2.5
unnamed: R34.2, R38.1, U2.7
unnamed: C24.2, D1.2, L4.2, U2.1
unnamed: C29.1, R37.2
unnamed: R52.1, R53.2, U11.3
unnamed: R49.2, R50.2, U10.3
unnamed: J1.2, R13.2, R15.1, U4.1
unnamed: LD1.1, R35.1
RESET: IC1.F3, J7.42, R22.2
RXPLL_CLK: C11.1, FR5.2, J7.89
RX_EN: IC1.A15, J7.47
Synt_INTR: IC7.F4, R3.2, U1.3
TCK_FPGA: IC1.H3, J3.5, R32.1
TCK_FX3: IC7.F6, J3.2
TDI_FPGA: IC1.H4, J3.9, R30.1
TDI_FX3: IC7.E7, J3.6
TDO_FPGA: IC1.J4, J3.1, R31.2
TDO_FX3: IC7.C10, J3.10
TMS_FPGA: IC1.J5, J3.3
TMS_FX3: IC7.E8, J3.4
TRST_N_FX3: IC7.B11, J3.12
TXNRX1: IC1.F5, J7.65
TXNRX2: IC1.G5, J7.63
TXPLL_CLK: C12.1, FR8.2, J7.35
TX_EN: IC1.A13, J7.48
VCC1P2: C70.1, C71.1, C72.1, C73.1, C74.1, C75.1, C76.1, C77.1, C78.1, C79.1, C120.1, D4.1, FB3.1, FB4.1, FR2.1, IC1.G6, IC1.G7, IC1.G8, IC1.G9, IC1.G10, IC1.H6, IC1.H11, IC1.K7, L6.1, R65.1
VCC2P5: FB1.1, FB2.1, R66.2, R148.1, R151.1, R154.1
VREF_B3_B4: C113.1, C114.1, C143.1, C144.1, IC1.P6, IC1.P11, IC3.J2, IC4.6
VTT_SDRAM: C141.1, C142.1, C146.1, C147.1, C148.1, C149.1, C150.1, C151.1, IC4.3, IC4.5, R72.1, R73.1, R74.1, R75.1, R76.1, R77.1, R78.1, R79.1, R80.1, R81.1, R82.1, R83.1, R84.1, R85.1, R86.1, R87.1, R88.1, R89.1, R90.1, R91.1, R92.1, R93.1, R94.1, R95.1, R96.1, R97.1, R98.1, R99.1, R100.1, R101.1, R102.1, R103.1, R104.1, R105.1, R106.1, R107.1, R108.1, R109.1, R110.1, R111.1, R112.1

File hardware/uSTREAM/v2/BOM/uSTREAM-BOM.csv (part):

0.33UF_0603	2	"C24 C115"	SMD0603	Farnell	1759404RL	MULTICOMP	MCCA000526	MLCC 0603 X5R 16V 0.33UF	0.33uF
2.2NF_0402	2	"C29 C122"	SMD0402	Digi-Key	1276-1054-1-ND	Samsung Electro-Mechanics America, Inc	CL05B222KB5NNNC	CAP CER 2200PF 50V 10% X7R 0402	2.2nF
4.7UF_0603	8	"C118 C119 C152 C153 C227 C228 C229 C230"	SMD0603	Digi-Key	1276-2087-1-ND	Samsung Electro-Mechanics America, Inc.	CL10B475KQ8NQNC	CAP CER 4.7UF 6.3V X7R 0603	4.7uF
100NF_0402	31	"C113 C114 C124 C125 C126 C127 C128 C129 C130 C131 C132 C133 C134 C135 C136 C137 C138 C139 C143 C144 C146 C147 C148 C149 C150 C151 C155 C156 C161 C162 C163"	C_SM0402	DigiKey	399-3027-1-ND	KEMET	C0402C104K8PACTU	CAP, CER, 0.1UF, 10V, 10%, X5R, 0402,	100nF
1UF_0402	1	"C140"	C_SM0402	Digi-Key	311-1377-1-ND	Yageo	CC0402ZRY5V5BB105	CAP, CER, 1UF, 6.3V, Y5V, 0402,	1uF
1UF_0402	1	"C157"	C_SM0402	Digi-Key	490-6298-1-ND	Murata Electronics North America	GRM155R61A105KE15J	CAP, CER, 1UF, 10V, 10%, X5R, 0402,	1uF
13PF_0402	2	"C158 C159"	C_SM0402	DigiKey	490-5925-1-ND	Murata Electronics North America	GRM1555C1H130JA01D	CAP CER, 13PF, 50V, 5%, NPO, 0402,	13pF
10NF_0402	13	"C165 C177 C179 C181 C184 C185 C187 C196 C198 C199 C200 C201 C202"	C_SM0402	DigiKey	311-1349-1-ND	Yageo	CC0402KRX7R9BB103	CAP CER, 10000PF, 50V, 10%, X7R, 0402,	10nF
100NF_0402	17	"C166 C170 C172 C174 C176 C178 C180 C182 C183 C186 C188 C189 C190 C191 C192 C193 C194"	C_SM0402	DigiKey	399-3027-1-ND	KEMET	C0402C104K8PACTU	CAP, CER, 0.1UF, 10V, 10%, X5R, 0402,	100nF
10UF_0805	3	"C123 C141 C142"	C_SM0805	Digi-Key	445-11388-1-ND	TDK Corporation	C2012JB0J106K125AB	CAP CER, 10UF, 6.3V, 10%, JB, 0805,	10uF
22UF_0805	4	"C164 C168 C169 C171"	C_SM0805	Digi-Key	587-1958-1-ND	Taiyo Yuden	LMK212BJ226MG-T	CAP CER, 22UF, 10V, 20%, X5R, 0805,	22uF
100UF_1206	4	"C14 C70 C86 C100"	C_SM1206	DigiKey	490-4539-1-ND	Murata Electronics North America	GRM31CR60J107ME39L	CAP CER, 100UF, 6.3V, 20%, X5R, 1206,	100uF
100UF_1206_NF	1	"C15"	C_SM1206	DigiKey	490-4539-1-ND	Murata Electronics North America	GRM31CR60J107ME39L	CAP CER, 100UF, 6.3V, 20%, X5R, 1206,	100uF NF	NOFIT
10NF_0402	7	"C71 C74 C77 C80 C83 C94 C97"	SM0402	DigiKey	311-1349-1-ND	Yageo	CC0402KRX7R9BB103	CAP CER, 10000PF, 50V, 10%, X7R, 0402,	10nF
100PF_0402	5	"C4 C5 C8 C9 C10"	SMD0402	Digi-Key	311-1024-1-ND	Yageo	CC0402JRNPO9BN101	CAP CER, 100PF, 50V, 5%, NPO, 0402,	100pF
150PF_0402	2	"C11 C12"	SMD0402	Digi-Key	587-1213-1-ND	Taiyo Yuden	UMK105CG151JV-F	CAP CER 150PF 50V NP0 0402	150pF
1UF_0402	14	"C16 C17 C20 C33 C34 C35 C36 C73 C76 C79 C82 C85 C96 C99"	SMD0402	Digi-Key	311-1377-1-ND	Yageo	CC0402ZRY5V5BB105	CAP, CER, 1UF, 6.3V, Y5V, 0402,	1uF
100NF_0402	31	"C18 C19 C21 C22 C23 C44 C64 C72 C75 C78 C81 C84 C87 C88 C89 C90 C91 C92 C95 C98 C101 C102 C103 C104 C105 C106 C107 C108 C109 C110 C112"	SMD0402	DigiKey	311-1047-1-ND	Yageo	CC0402ZRY5V7BB104	CAP, CER, 0.1UF, 16V, Y5V, 0402,	100nF
22NF_0402	2	"C26 C117"	SMD0402	DigiKey	311-1378-1-ND	Yageo	CC0402KRX7R9BB103	CAP CER, 0.022UF, 16V, 10%, X7R, 0402,	22nF
22PF_0402	2	"C28 C121"	SMD0402	DigiKey	311-1018-1-ND	Yageo	CC0402JRNPO9BN220	CAP CER, 22PF, 50V, 5%, NPO, 0402,	22pF
10UF_0603	1	"C32"	SMD0603	Digi-Key	311-1448-1-ND	Yageo	CC0603MRX5R5BB106	CAP, CER, 10UF, 6.3V, 20%, X5R, 0603,	10uF
22UF_0805	10	"C1 C3 C6 C7 C13 C27 C30 C31 C120 C203"	SMD0805	Digi-Key	445-1422-1-ND	TDK Corporation	C2012X5R0J226M125AC	CAP CER, 22UF, 6.3V, 20%, X5R, 0805,	22uF
10UF_1206	2	"C25 C116"	SMD1206	Digi-Key	311-1376-1-ND	Yageo	CC1206ZKY5V7BB106	CAP, CER, 10UF, 16V, Y5V, 1206,	10uF
TS4148	2	"D3 D4"	SM0805	Farnell	8150206RL	TAIWAN SEMICONDUCTOR	TS4148 RY	DIODE 0.5A 0805 100V	TS4148
20BQ030	2	"D1 D2"	SMB	Digi-Key	20BQ030PBFCT-ND	Vishay Semiconductor Diodes Division	VS-20BQ030TRPBF	DIODE SCHOTTKY, 30V, 2A, DO214AA,	20BQ030
SHIELD_16.5X16.5MM	1	"EK2"	shield_16.5x16.5mm	Digi-Key	903-1051-1-ND	Laird Technologies EMI	BMI-S-202-F	BOARD SHIELD .65X.65" FRAME
SHIELD_60X30MM_CUSTOM	1	"EK1"	shield_60x30mm_custom
FB_600R_0402	4	"FB1 FB2 FB3 FB4"	SM0402	445-2162-1-ND	Digi-Key	FERRITE CHIP BEAD, 600 OHM, SMD,	MMZ1005S601C	TDK Corporation	600 Ohm @ 100MHz, 0.3A
FIDUCIAL	4	"FD1 FD2 FD3 FD4"	
FR_220R_0402	4	"FR5 FR6 FR8 FR9"	R_SM0402	445-9329-1-ND	Digi-Key	FERRITE, CHIP, 220 OHM, 0402,	MPZ1005S221E	TDK Corporation	100MHz/220/0.9A
FR_600R_0805_2A	4	"FR2 FR3 FR4 FR7"	R_SM0805	Digi-Key	445-2206-1-ND	TDK Corporation	MPZ2012S601AT000	FERRITE, CHIP, BEAD, 600 OHM, SMD,	100MHz/600/2A
FR_220R_1206_4A	1	"FR10"	R_SM1206	587-3250-1-ND	Digi-Key	FERRITE BEAD 220 OHM 1206	FBMH3216HM221NT	Taiyo Yuden	100MHz/220/4A
RT9026GFP	1	"IC4"	10MSOP	Digi-Key	1028-1010-1-ND	Richtek USA Inc	RT9026GFP	IC DDR TERMINATION REG 10MSOP	RT9026GFP
CYUSB3013	1	"IC7"	121-TFBGA	Mouser	727-CYUSB3013-BZXC	Cypress Semiconductor	CYUSB3013-BZXC	USB Interface, IC EZUSB, SuperSpeedCtrl X16, 256KB,	CYUSB3013
EP4CE10F17C8N	1	"IC1"	256FBGA	Digi-Key	544-2830-ND	Altera	EP4CE10F17C8N	IC FPGA 179 I/O 256FBGA	EP4CE10F17C8N
FLASH_4MBIT_2X3MM_3.3V	2	"IC8 IC9"	8-USON	Digi-Key	1092-1064-ND	Macronix	MX25L4006EZUI-12G	IC FLASH 4MBIT 86MHZ 8USON	MX25L4006EZUI-12G
W9751G6KB-25	1	"IC3"	84WBGA	Digi-Key	W9751G6KB-25-ND	Winbond Electronics	W9751G6KB-25	IC, DDR2, SDRAM, 512M, 2.5NS, 84WBGA,	W9751G6KB-25
SP3010-04UTG	1	"IC6"	uDFN-10	Digi-Key	F3507TR-ND	Littelfuse Inc	SP3010-04UTG	TVS ARRAY, ESD, 4CH, .45PF, 8KV, UDFN,	SP3010-04UTG
100-PIN_CONN_HDR	1	"J7"	100-PIN_CONNECTOR	Digi-Key	H11614CT-ND	Hirose Electric Co Ltd	DF40C-100DP-0.4V(51)	CONN HDR 100POS 0.4MM SMD GOLD
PINHEADER2X20_SMD_FEMALE	1	"J2"	Pin Header 2 x 20 SMD	Digi-Key	S5690-ND	Sullins Connector Solutions	NPTC202KFMS-RC	CONN FEMALE 40POS DL .1" TIN SMD	Female Socket 2 x 20 SMD
PINHEADER2X7_SMD_1.27MM	1	"J3"	PinHeader2x7_SMD_1.27mm	Digi-Key	609-3730-ND	FCI	20021121-00014T4LF	CONN HEADER 14POS DL UNSHRD SMD	PinHeader2x7_SMD_1.27mm
JUMPER2_V	1	"J1"	PINHEADER_1x2_SMD	Digi-Key	952-1913-ND	Harwin Inc	M20-8770246	2POS SIL VERTICAL SMT HEADER	NOFIT
PINHEADER1X2_SMD_RIGHT	1	"J5"	PINHEADER_1x2_SMD_right	Digi-Key	S1113E-02-ND	Sullins Connector Solutions	GEC02SBSN-M89	CONN HEADER 2POS .100 RT/A SMD
USB3_A_SMD	1	"J4"	USB3_A_SMD	Farnell	2443106	GLOBAL CONNECTOR TECHNOLOGY	USB1065-30-A	Connector Plug USB TypeA 3.0, Superspeed+ 9 Position Surface Mount, Right Angle, Horizontal	USB3_A
2.2UH_XAL60XX_SERIES	1	"L4"	XAL60xx series	Coilcraft	XAL6030-222MEB	Coilcraft	XAL6030-222MEB	SMT power inductor 2.2 uH	2.2uH
22UH_0603	1	"L3"	SMD0603	Digi-Key	445-17069-1-ND	TDK Corporation	MLZ1608N220LT000	FIXED IND 22UH 300MA 1.65 OHM	22uH
22UH_XAL60XX_SERIES_NF	1	"L5"	XAL60xx series	Coilcraft	XAL6060-223MEB	Coilcraft	XAL6060-223MEB	SMT power inductor 22 uH	22uH NF	NOFIT
22UH_XAL60XX_SERIES	1	"L6"	XAL60xx series	Coilcraft	XAL6060-223MEB	Coilcraft	XAL6060-223MEB	SMT power inductor 22 uH	22uH
LED	1	"LD1"	LD0603	Farnell	1226372RL	OSRAM	LGQ971	OSRAM - LGQ971 - LED; SMD; GREEN;
LED_0603_YELLOW	6	"LD2 LD3 LD4 LD5 LD6 LD7"	LD_0603	DigiKey	160-1836-1-ND	Lite-On Inc	LTST-C194KSKT	LED, YELLOW, RECT, CLEAR, 0603,	Yellow
0R_0402	13	"R9 R21 R66 R115 R132 R147 R150 R153 R156 R157 R159 R161 R163"	R_SM0402	Digi-Key	311-0.0JRCT-ND	Yageo	RC0402JR-070RL	RES, 0.0 OHM,1/16W, JUMP, 0402 SMD,	0R
0R_0402_NF	5	"R20 R122 R148 R151 R154"	R_SM0402	Digi-Key	311-0.0JRCT-ND	Yageo	RC0402JR-070RL	RES, 0.0 OHM,1/16W, JUMP, 0402 SMD,	0R	NF	NOFIT
0R_0402	2	"R48 R51"	SM0402	Farnell	1469661	VISHAY DRALORIC	CRCW04020000Z0ED	R 0 Ohm 1% 63mW 0402	0R
0R_0805	2	"R13 R15"	SM0805	Digi-Key	P0.0ACT-ND	Panasonic Electronic Components	ERJ-6GEY0R00V	RES 0.0 OHM 1/8W JUMP 0805 SMD	0R
0R_0402	1	"R18"	SMD0402	Digi-Key	311-0.0JRCT-ND	Yageo	RC0402JR-070RL	RES, 0.0 OHM,1/16W, JUMP, 0402 SMD,	0R
56R_0201	41	"R72 R73 R74 R75 R76 R77 R78 R79 R80 R81 R82 R83 R84 R85 R86 R87 R88 R89 R90 R91 R92 R93 R94 R95 R96 R97 R98 R99 R100 R101 R102 R103 R104 R105 R106 R107 R108 R109 R110 R111 R112"	SMD0201	Digi-Key	1276-3594-1-ND	Samsung Electro-Mechanics America, Inc	RC0603F560CS	RES 56 OHM 1/20W 1% 0201	56R
200R/1%_0402	1	"R138"	R_SM0402	Digi-Key	311-200LRCT-ND	Yageo	RC0402FR-07200RL	RES, 200 OHM, 1/16W, 1%, 0402 SMD,	200R/1%
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
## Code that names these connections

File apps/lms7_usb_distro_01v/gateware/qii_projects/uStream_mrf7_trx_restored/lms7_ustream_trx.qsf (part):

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set_global_assignment -name OUTPUT_IO_TIMING_FAR_END_VMEAS "HALF SIGNAL SWING" -rise
set_global_assignment -name OUTPUT_IO_TIMING_FAR_END_VMEAS "HALF SIGNAL SWING" -fall
set_global_assignment -name GENERATE_RBF_FILE ON
set_location_assignment PIN_F6 -to FX3_SPI_MISO
set_location_assignment PIN_F7 -to FX3_SPI_MOSI
set_location_assignment PIN_B7 -to FX3_SPI_SCK
set_location_assignment PIN_A2 -to FPGA_LMS_CS
set_location_assignment PIN_E6 -to FPGA_SPI_MISO
set_location_assignment PIN_A5 -to FPGA_SPI_MOSI
set_location_assignment PIN_E7 -to FPGA_SPI_SCK
set_location_assignment PIN_B5 -to FPGA_DAC_CS
set_location_assignment PIN_A4 -to FX3_FPGA_GPIO1
set_location_assignment PIN_F3 -to LMS_RESET
set_location_assignment PIN_D8 -to RPI_GPIO12_miso
set_location_assignment PIN_E8 -to RPI_GPIO16_cs
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set_global_assignment -name ENABLE_OCT_DONE OFF
set_global_assignment -name ENABLE_CONFIGURATION_PINS OFF
set_global_assignment -name ENABLE_BOOT_SEL_PIN OFF
set_location_assignment PIN_D16 -to FX3_PCLK
set_location_assignment PIN_G11 -to FX3_DQ[15]
set_location_assignment PIN_N13 -to FX3_DQ[3]
set_location_assignment PIN_M12 -to FX3_DQ[10]
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set_location_assignment PIN_L15 -to FX3_DQ[11]
set_location_assignment PIN_J11 -to FX3_DQ[5]
set_location_assignment PIN_K16 -to FX3_DQ[14]
set_location_assignment PIN_A3 -to FX3_FPGA_GPIO3
set_location_assignment PIN_F16 -to FX3_DQ[2]
set_location_assignment PIN_B16 -to FX3_FLAGA
set_location_assignment PIN_F15 -to FX3_FLAGB
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set_location_assignment PIN_M8 -to mem_dm[1]
set_location_assignment PIN_M7 -to mem_dqs[0]
set_location_assignment PIN_T7 -to mem_dqs[1]
set_location_assignment PIN_A6 -to FX3_FPGA_SNN
set_location_assignment PIN_E9 -to RPI_GPIO19
set_location_assignment PIN_F10 -to RPI_GPIO26
set_location_assignment PIN_D9 -to RPI_GPIO6
set_location_assignment PIN_F11 -to RPI_GPIO13
set_location_assignment PIN_B8 -to FX3_GPIO5
set_global_assignment -name ENABLE_SIGNALTAP OFF
set_global_assignment -name USE_SIGNALTAP_FILE signal_tap/pll_phase.stp
set_location_assignment PIN_A9 -to RPI_MISO
set_location_assignment PIN_B10 -to RPI_MOSI
set_location_assignment PIN_A8 -to RPI_SCLK
set_location_assignment PIN_D14 -to RPI_SDA1
set_location_assignment PIN_B13 -to RPI_GCLK
set_location_assignment PIN_D12 -to RPI_GEN0
set_location_assignment PIN_A11 -to RPI_GEN3
set_global_assignment -name DEVICE_MIGRATION_LIST "EP4CE10F17C8,EP4CE6F17C8"
set_location_assignment PIN_B11 -to RPI_GEN4
set_location_assignment PIN_D11 -to RPI_ID_SD
set_global_assignment -name PARTITION_NETLIST_TYPE SOURCE -section_id Top
set_global_assignment -name PARTITION_FITTER_PRESERVATION_LEVEL PLACEMENT_AND_ROUTING -section_id Top
set_global_assignment -name PARTITION_COLOR 16764057 -section_id Top
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set_instance_assignment -name IO_STANDARD "3.3-V LVCMOS" -to FPGA_SPI_MOSI
set_instance_assignment -name IO_STANDARD "3.3-V LVCMOS" -to FPGA_SPI_SCK
set_instance_assignment -name IO_STANDARD "3.3-V LVCMOS" -to FPGA_DAC_CS
set_instance_assignment -name IO_STANDARD "3.3-V LVCMOS" -to FX3_FPGA_GPIO1
set_instance_assignment -name IO_STANDARD "3.3-V LVCMOS" -to LMS_RESET
set_instance_assignment -name IO_STANDARD "3.3-V LVCMOS" -to RPI_GPIO12_miso
set_instance_assignment -name IO_STANDARD "3.3-V LVCMOS" -to RPI_GPIO16_cs
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set_instance_assignment -name IO_STANDARD "3.3-V LVCMOS" -to TXD[1]
set_instance_assignment -name IO_STANDARD "3.3-V LVCMOS" -to TXD[0]
set_instance_assignment -name IO_STANDARD "3.3-V LVCMOS" -to TXIQSEL
set_instance_assignment -name IO_STANDARD "3.3-V LVCMOS" -to FX3_FPGA_GPIO3
set_instance_assignment -name IO_STANDARD "1.8 V" -to FX3_A[1]
set_instance_assignment -name IO_STANDARD "1.8 V" -to FX3_A[0]
set_instance_assignment -name IO_STANDARD "1.8 V" -to FX3_DQ[15]
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set_instance_assignment -name OUTPUT_ENABLE_GROUP 3078784 -to mem_dm[1]
set_instance_assignment -name CKN_CK_PAIR ON -from mem_clk_n[0] -to mem_clk[0]
set_instance_assignment -name IO_STANDARD "3.3-V LVCMOS" -to FX3_FPGA_SNN
set_instance_assignment -name IO_STANDARD "3.3-V LVCMOS" -to RPI_GPIO19
set_instance_assignment -name IO_STANDARD "3.3-V LVCMOS" -to RPI_GPIO26
set_instance_assignment -name IO_STANDARD "3.3-V LVCMOS" -to RPI_GPIO6
set_instance_assignment -name IO_STANDARD "3.3-V LVCMOS" -to RPI_GPIO13
set_instance_assignment -name IO_STANDARD "3.3-V LVCMOS" -to FX3_GPIO5
set_instance_assignment -name IO_STANDARD "3.3-V LVCMOS" -to RPI_MISO
set_instance_assignment -name IO_STANDARD "3.3-V LVCMOS" -to RPI_MOSI
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set_instance_assignment -name IO_STANDARD "3.3-V LVCMOS" -to RPI_GEN3
set_instance_assignment -name IO_STANDARD "3.3-V LVCMOS" -to RPI_GEN4
set_instance_assignment -name IO_STANDARD "3.3-V LVCMOS" -to RPI_ID_SD
set_location_assignment PIN_C2 -to MCLK2
set_instance_assignment -name IO_STANDARD "3.3-V LVCMOS" -to MCLK2
set_location_assignment PIN_D2 -to FCLK2
set_instance_assignment -name IO_STANDARD "3.3-V LVCMOS" -to FCLK2
set_location_assignment PIN_N1 -to MCLK1
set_location_assignment PIN_K2 -to FCLK1
set_instance_assignment -name IO_STANDARD "3.3-V LVCMOS" -to MCLK1
set_instance_assignment -name IO_STANDARD "3.3-V LVCMOS" -to FCLK1
set_location_assignment PIN_D6 -to unused_pin
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
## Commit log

2015-03-24 Renamed stream_openrisc_v2 directory
2015-03-24 wb_ram: Add license header
2015-03-24 Fix license headers for or1k_bootloaders
2015-03-24 Added Lime (c) notices and license info
2015-03-25 stream: Connect LMS TX interface
2015-03-25 myriadrf: Improve TX interface timing
2015-03-25 stream: Remove unused files
2015-03-25 myriadrf.core: Remove non-existent file
2015-03-25 Add pin mapping for Stream v2 boards
2015-03-25 Add internal SPI master
2015-03-25 Update and regenerate documentation
2015-03-25 Add more sw drivers
2015-03-25 Move rx_dma example to a subdirectory
2015-03-25 Remove leftovers from rx_dma move
2015-03-25 Update Linux kernel URL in docs
2015-03-25 Add license headers to files in quartus project
2015-03-25 Added README
2015-03-25 Update README.md
    Added description of sw directory
2015-03-26 Added LMS7002EVB examples
2015-03-26 Added enclosure design
2015-03-26 Added photo
2015-03-27 or1k_bootloaders: Remove non-existent file
2015-03-27 myriadrf: Properly align IQ sel to data in RX interface
2015-03-27 Regenerate Quartus project and sof file
2015-04-08 Added documentation
2015-04-13 Added enclosure Solidworks and IGES CAD files
2015-04-13 Re-converted LMS7EVB docs from Word to ODT to fix formatting issues
2015-12-03 Added uSTREAM hardware design and examples

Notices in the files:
apps/lms7_usb_distro_01v/gateware/qii_projects/uStream_mrf7_trx_restored/lms7_ustream_trx.qsf:
Copyright (C) 1991-2014 Altera Corporation
